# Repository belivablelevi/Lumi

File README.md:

# Lumi

**An open-source, build-it-yourself robot keychain pet.** A tiny glowing face
that feels your pats and shakes, has moods, sleeps when you put it down,
wakes when you pick it up, and plays ping-pong with a friend's
Lumi over the air.

Lumi is an independent DIY recreation of the *kind* of gadget popularised by
the Rekko NEO keychain. It's built from ~$15 of off-the-shelf modules. It
shares no code, artwork or branding with Rekko and isn't affiliated with it.

| Spec card item | Lumi |
|---|---|
| 0.96" OLED, 128×64, glowing cyan | SSD1306 0.96" 128×64 (blue panel reads as cyan) |
| Motion sensor, 6-axis, feels every pat & shake | MPU-6050: pat, double-pat, pat-spam, shake, drop, tilt, flip, pick-up, put-down |
| ESP32-C3 brain, runs 60+ animations | XIAO ESP32C3 · **64 animations** from 29 parametric expressions, plus blinking, eye-darts and breathing on top |
| 2-player wireless battle | **Tilt Pong** over ESP-NOW: classic Pong across two screens. Tilt to move your paddle, pat to smash, first to 5 |
| Battery inside | 702025 300 mAh LiPo (the case can be resized for others) |
| USB-C rechargeable | XIAO's USB-C + on-board charger |
| Deep-sleeps when idle | ESP32-C3 deep sleep, display off, IMU on wake-on-motion |
| Wakes when you pick it up | MPU-6050 motion interrupt → GPIO3 deep-sleep wake |
| Free animation updates | Wi-Fi update mode: phone → `192.168.4.1` → upload |
| 35 × 37 mm glitter shell | Parametric OpenSCAD snap-fit case, 35 × 37 × 25.5 mm, print in glitter PLA |

## What it looks like

All 29 expressions (rendered by the real firmware code in the simulator):

Menu, battery, update and Tilt Pong screens:

A scripted session: boot, pats, shake, menu, a full Tilt Pong match, falling asleep
([tour.gif](docs/previews/tour.gif)).

## Every Lumi is one of a kind

Each unit has its own eyes, highlight, accent and temperament: 108,000
combinations, with common, uncommon, rare and legendary units. A unit gets
its personality automatically from its chip ID. Makers can also assign
one at the factory with **Lumi Studio**, a desktop app (Windows, macOS,
Linux) for:

- designing new faces and animations,
- generating batches of unique units with a rarity mix you choose,
- writing each unit's persona over USB and recording it in a manifest.

See [docs/studio.md](docs/studio.md).

## The website

`web/` is the Snaggo storefront for Lumi, at [snaggo.tech](https://snaggo.tech). It's a Next.js site with pre-orders through Stripe, launch emails, and the
firmware's real animations playing on every screen. See [web/README.md](web/README.md).

## Repository layout

```
firmware/
  platformio.ini            PlatformIO project (XIAO ESP32C3)
  src/                      hardware glue: main.cpp, OLED + IMU drivers, config.h (pins & tuning)
  lib/lumi_core/src/        portable brain, no Arduino dependencies:
    face.*                    parametric face renderer + 29 expressions
    animations.*              64 animations (data tables; add your own here or in Lumi Studio)
    genes.*                   per-unit looks, temperament and rarity
    pack.*                    emotion packs: custom faces, animations and a persona
    serial_cmd.*              USB provisioning protocol
    animator.*                tweening, blinking, eye darts, motion layers
    gestures.*                pat / shake / tilt / pickup / freefall detection
    mood.h                    happiness + energy, persisted across deep sleep
    pong.*                    Tilt Pong: pairing, ball hand-off over the radio, scoring
    app.*                     behaviour: modes, menu, sleep rules, screens
    gfx.*                     1-bit framebuffer + 5x7 font
hardware/
  BOM.md · wiring.md
  enclosure/lumi_case.scad  parametric case; stl/ has ready-to-print parts
docs/
  using-lumi.md             gestures, mood, menu, Tilt Pong, OTA, serial console
  assembly.md               build guide + first-power-up checklist
  studio.md                 Lumi Studio guide for makers
  previews/                 rendered images
tests/                      desktop tests for the core (make -C tests)
tools/
  sim/                      desktop simulator → PNG/GIF previews
  studio/                   Lumi Studio desktop app (PySide6) + liblumicore C API + virtual Lumi
web/                        the Snaggo website (Next.js storefront, pre-orders, launch signups)
  arduino_build.sh          build with arduino-cli / Arduino IDE instead of PlatformIO
```

## Build the firmware

**PlatformIO** (recommended):

```sh
cd firmware
pio run -t upload        # build + flash over USB-C
pio device monitor       # serial console (type 'h' for commands)
```

**arduino-cli / Arduino IDE** (ESP32 core 2.0.17):

```sh
tools/arduino_build.sh                # compile
tools/arduino_build.sh /dev/ttyACM0   # compile + upload
```

Using an **ESP32-S3 SuperMini** instead of the XIAO? Build with
`pio run -e esp32s3_supermini -t upload`, and see the S3 section of
[`hardware/wiring.md`](hardware/wiring.md#alternative-esp32-s3-supermini) for its
pins, power options and the matching case setting.

If the XIAO doesn't show up as a serial port, hold **BOOT**, tap **RESET**,
release **BOOT**, then upload again.

## Hack on it without hardware

The behaviour runs on your computer exactly as it does on the device:

```sh
make -C tests                         # 819 checks: gestures, pong, animations, genes, packs, app flows
python3 tools/sim/make_previews.py    # re-render docs/previews (needs Pillow)
python3 tools/sim/make_previews.py --all-gifs   # one GIF per animation in build/sim/gifs
```

Adding an animation is a few lines in `firmware/lib/lumi_core/src/animations.cpp`:
a list of `(expression, gaze, motion, tween ms, hold ms, effects)` keys
plus a table row saying which gesture triggers it and in which mood range.

## How it works (short version)

- **Face**: a face is ~20 numbers (eye size, lids, slant, cheeks, gaze, mouth
  shape…). Expressions are presets, and animations tween between them.
  Blinks, eye darts and breathing are layered on top, so Lumi never looks
  frozen.
- **Gestures**: the MPU-6050 samples at 100 Hz into its FIFO. The firmware
  high-passes the signal. Short sharp bursts are pats, repeated big bursts
  are shakes. Low-passed gravity gives orientation; |a| ≈ 0 is free-fall.
  Tap timestamps come from the FIFO cadence, so they stay accurate even
  while the display is being redrawn.
- **Tilt Pong**: ESP-NOW broadcast, no pairing. The Lumi with the higher
  MAC hosts and serves first. Tilt steers the paddle (low-passed gravity
  X). Only the Lumi the ball is on decides whether it was hit, so radio latency just makes the flight a little longer. Each
  ball crossing the net carries a sequence number plus its position, angle
  and speed, and each Lumi's miss count only ever grows. Packets repeat
  ~10 times a second, so lost ones only add delay. The tests play whole
  matches, and 90-second rallies, over a simulated link with 40% packet loss.
- **Sleep**: display charge pump off, IMU to low-power cycle mode with a
  latched motion interrupt on GPIO3, ESP32-C3 into deep sleep. Mood lives
  in RTC memory, and the RTC clock tells Lumi how long it slept.

## Status

- ✅ Core logic: 819 automated checks pass (ASan/UBSan clean), including
  two simulated Lumis playing complete Tilt Pong matches through their menus.
- ✅ Lumi Studio: 13 tests drive every tab offscreen and provision a virtual
  Lumi end to end. The packaged Linux app was built and started here. CI
  builds Windows and macOS too, but they haven't been tried by a person yet.
- ✅ Firmware compiles and links for the ESP32-C3 and ESP32-S3 (Arduino core
  2.0.17, `-Wall -Wextra`, no warnings in Lumi's code). On the C3 it uses
  812 KB of flash (63% of an OTA slot) and 87 KB of RAM.
- ✅ Case renders to valid STLs at 35 × 37 mm.
- ⚠️ **Not yet tested on real hardware.** Expect to tune the IMU axis map,
  tap threshold and wake sensitivity once it's built (see the checklist in
  `docs/assembly.md`), and to adjust case tolerances after a test print.
- ⚠️ The case is 25.5 mm deep because a stock GY-521 board won't fit beside
  the XIAO. A custom PCB, or a smaller IMU breakout, could get it thinner.

## License

MIT, see [LICENSE](LICENSE).

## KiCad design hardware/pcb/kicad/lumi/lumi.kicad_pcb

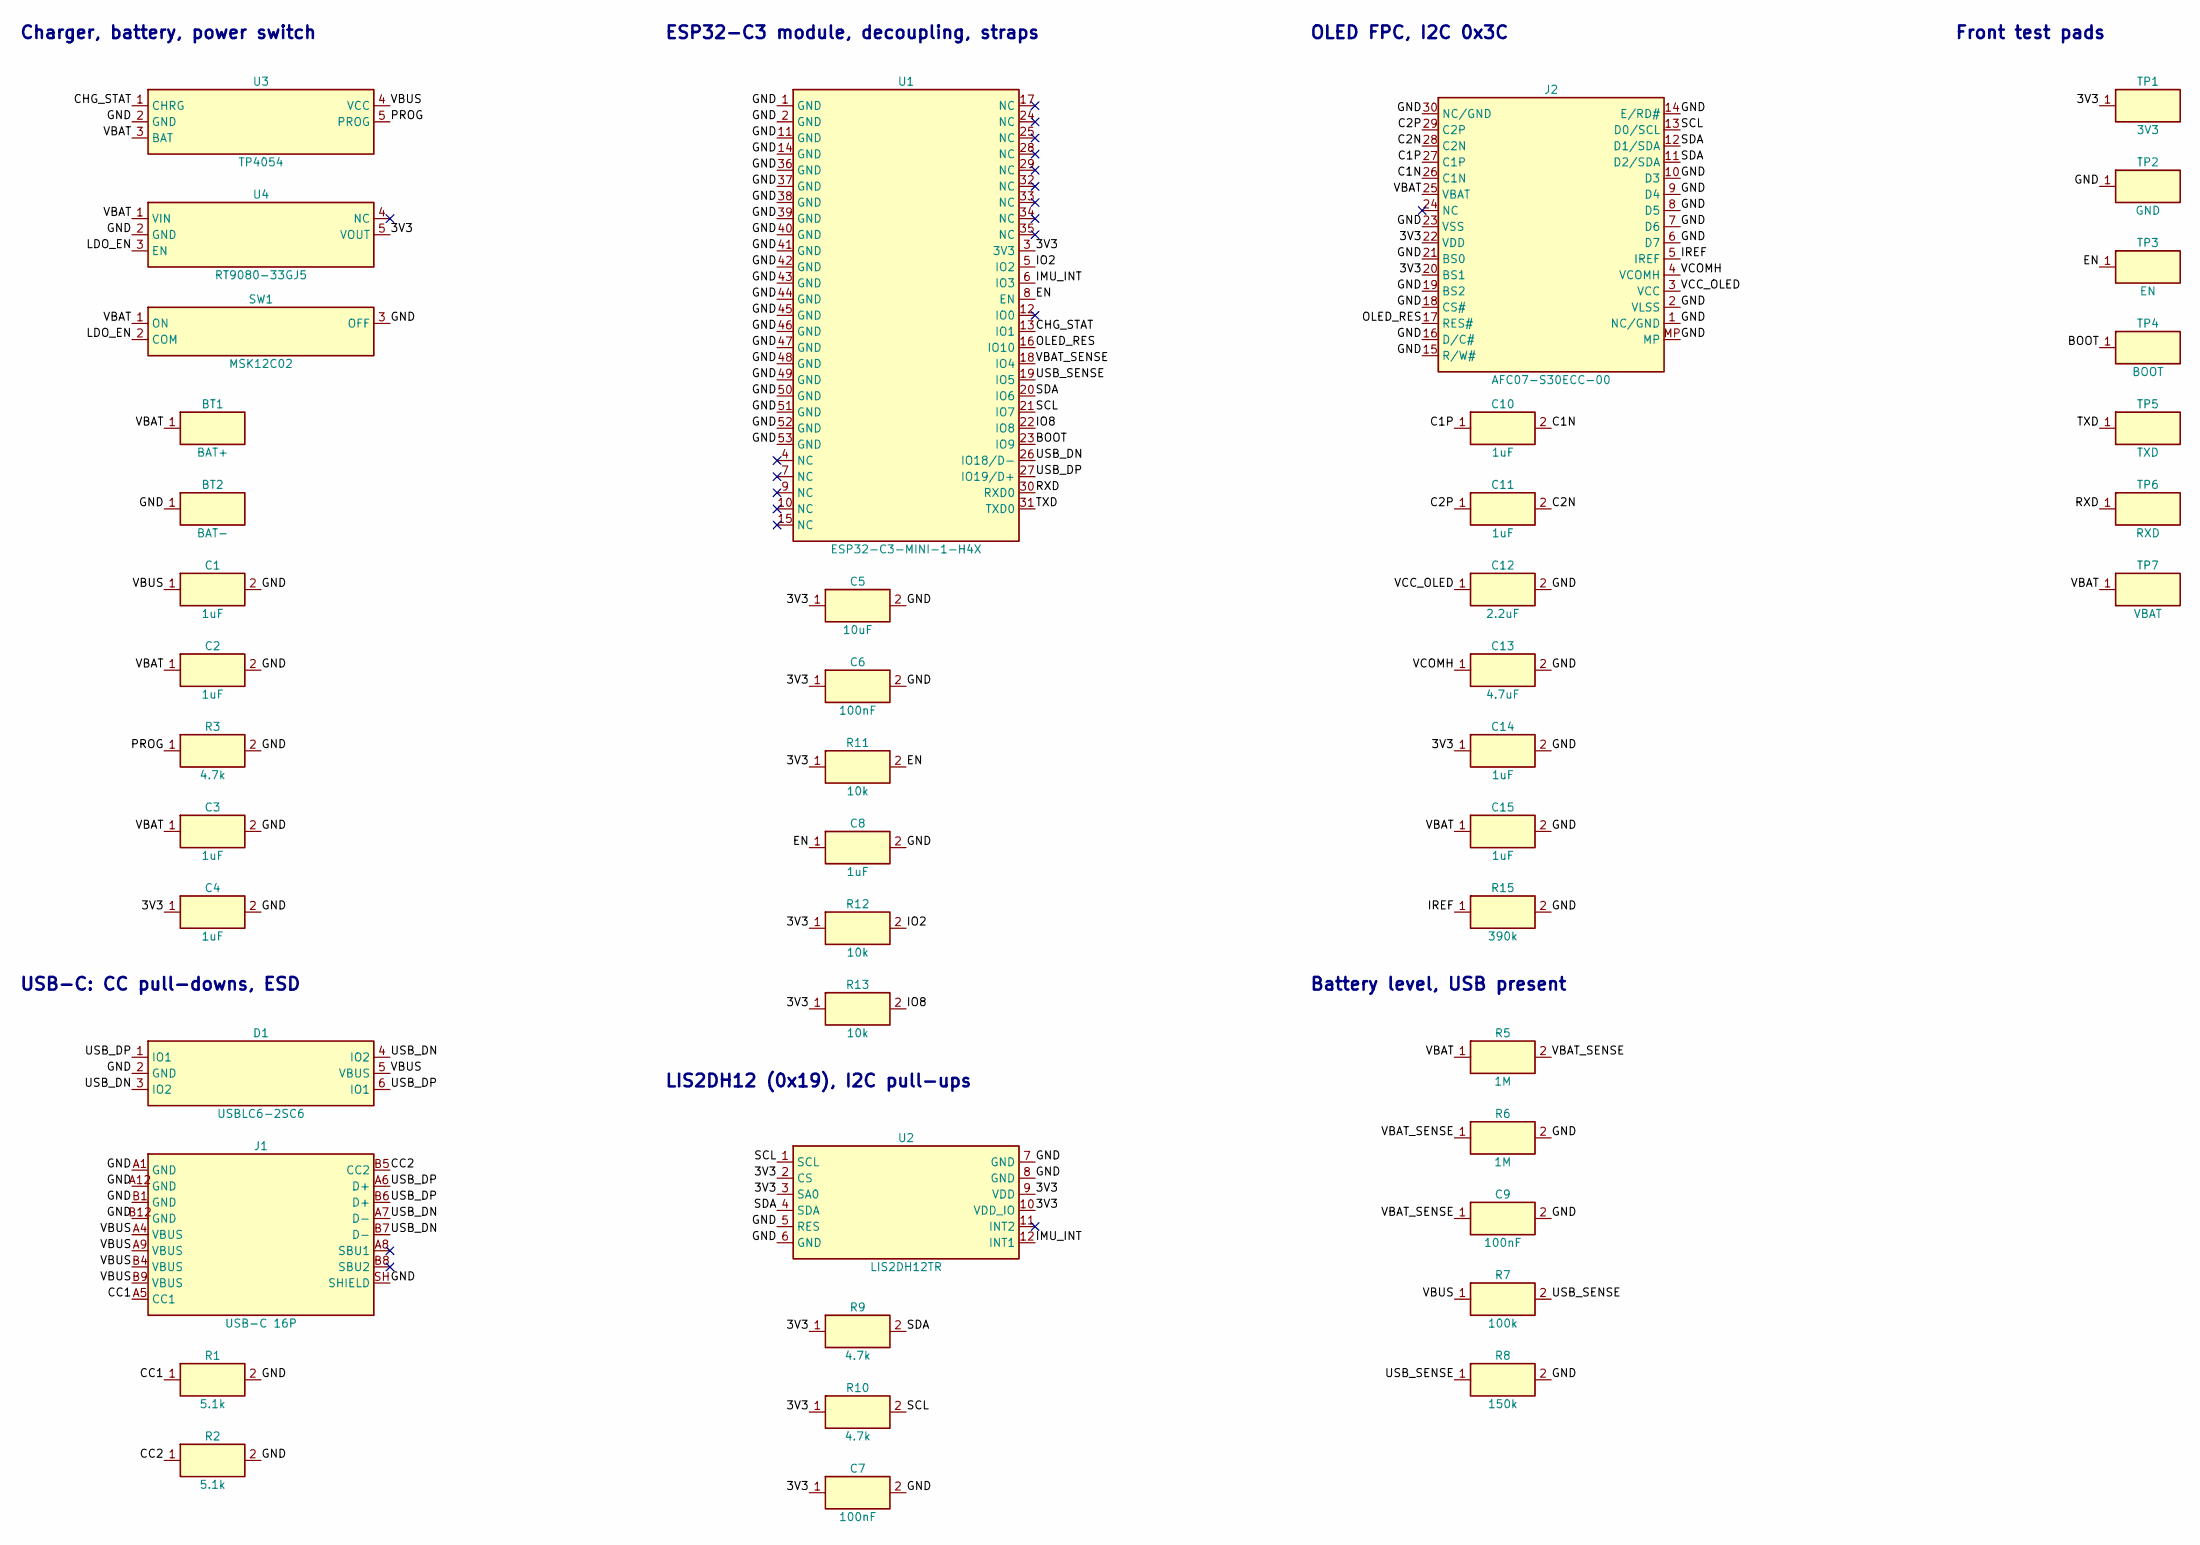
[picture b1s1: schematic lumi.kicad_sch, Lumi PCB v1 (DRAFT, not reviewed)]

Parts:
BT1: BAT+; TestPoint_Pad_1.5x1.5mm
BT2: BAT-; TestPoint_Pad_1.5x1.5mm
C1, C2, C3, C4, C8, C10, C11, C14, C15: 1uF; C_0402_1005Metric; LCSC C52923
C5: 10uF; C_0402_1005Metric; LCSC C15525
C6, C7, C9: 100nF; C_0402_1005Metric; LCSC C1525
C12: 2.2uF; C_0603_1608Metric; LCSC C23630
C13: 4.7uF; C_0603_1608Metric; LCSC C19666
D1: USBLC6-2SC6; SOT-23-6; LCSC C7519
J1: USB-C 16P; USB_C_Receptacle_HRO_TYPE-C-31-M-12; LCSC C165948
J2: AFC07-S30ECC-00; JUSHUO_AFC07-S30ECC-00; LCSC C11095
R1, R2: 5.1k; R_0402_1005Metric; LCSC C25905
R3, R9, R10: 4.7k; R_0402_1005Metric; LCSC C25900
R5, R6: 1M; R_0402_1005Metric; LCSC C26083
R7: 100k; R_0402_1005Metric; LCSC C25741
R8: 150k; R_0402_1005Metric; LCSC C25755
R11, R12, R13: 10k; R_0402_1005Metric; LCSC C25744
R15: 390k; R_0402_1005Metric; LCSC C25782
SW1: MSK12C02; LCSC C431540
TP1: 3V3; TestPoint_Pad_D1.0mm
TP2: GND; TestPoint_Pad_D1.0mm
TP3: EN; TestPoint_Pad_D1.0mm
TP4: BOOT; TestPoint_Pad_D1.0mm
TP5: TXD; TestPoint_Pad_D1.0mm
TP6: RXD; TestPoint_Pad_D1.0mm
TP7: VBAT; TestPoint_Pad_D1.0mm
U1: ESP32-C3-MINI-1-H4X; ESP32-C3-MINI-1; LCSC C41349510
U2: LIS2DH12TR; LGA-12_2x2mm_P0.5mm; LCSC C110926
U3: TP4054; SOT-23-5; LCSC C32574
U4: RT9080-33GJ5; SOT-23-5; LCSC C841192

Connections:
3V3: C4.1, C5.1, C6.1, C7.1, C14.1, J2.20 (BS1), J2.22 (VDD), R9.1, R10.1, R11.1, R12.1, R13.1, TP1.1, U1.3 (3V3), U2.2 (CS), U2.3 (SA0), U2.9 (VDD), U2.10 (VDD_IO), U4.5 (VOUT)
BOOT: TP4.1, U1.23 (IO9)
C1N: C10.2, J2.26 (C1N)
C1P: C10.1, J2.27 (C1P)
C2N: C11.2, J2.28 (C2N)
C2P: C11.1, J2.29 (C2P)
CC1: J1.A5 (CC1), R1.1
CC2: J1.B5 (CC2), R2.1
CHG_STAT: U1.13 (IO1), U3.1 (CHRG)
EN: C8.1, R11.2, TP3.1, U1.8 (EN)
GND: BT2.1, C1.2, C2.2, C3.2, C4.2, C5.2, C6.2, C7.2, C8.2, C9.2, C12.2, C13.2, C14.2, C15.2, D1.2 (GND), J1.A1 (GND), J1.A12 (GND), J1.B1 (GND), J1.B12 (GND), J1.SH (SHIELD), J2.1 (NC/GND), J2.2 (VLSS), J2.6 (D7), J2.7 (D6), J2.8 (D5), J2.9 (D4), J2.10 (D3), J2.14 (E/RD#), J2.15 (R/W#), J2.16 (D/C#), J2.18 (CS#), J2.19 (BS2), J2.21 (BS0), J2.23 (VSS), J2.30 (NC/GND), J2.MP, R1.2, R2.2, R3.2, R6.2, R8.2, R15.2, SW1.3 (OFF), TP2.1, U1.1 (GND), U1.2 (GND), U1.11 (GND), U1.14 (GND), U1.36 (GND), U1.37 (GND), U1.38 (GND), U1.39 (GND), U1.40 (GND), U1.41 (GND), U1.42 (GND), U1.43 (GND), U1.44 (GND), U1.45 (GND), U1.46 (GND), U1.47 (GND), U1.48 (GND), U1.49 (GND), U1.50 (GND), U1.51 (GND), U1.52 (GND), U1.53 (GND), U2.5 (RES), U2.6 (GND), U2.7 (GND), U2.8 (GND), U3.2 (GND), U4.2 (GND)
IMU_INT: U1.6 (IO3), U2.12 (INT1)
IO2: R12.2, U1.5 (IO2)
IO8: R13.2, U1.22 (IO8)
IREF: J2.5 (IREF), R15.1
LDO_EN: SW1.2 (COM), U4.3 (EN)
OLED_RES: J2.17 (RES#), U1.16 (IO10)
PROG: R3.1, U3.5 (PROG)
RXD: TP6.1, U1.30 (RXD0)
SCL: J2.13 (D0/SCL), R10.2, U1.21 (IO7), U2.1 (SCL)
SDA: J2.11 (D2/SDA), J2.12 (D1/SDA), R9.2, U1.20 (IO6), U2.4 (SDA)
TXD: TP5.1, U1.31 (TXD0)
USB_DN: D1.3 (IO2), D1.4 (IO2), J1.A7 (D-), J1.B7 (D-), U1.26 (IO18/D-)
USB_DP: D1.1 (IO1), D1.6 (IO1), J1.A6 (D+), J1.B6 (D+), U1.27 (IO19/D+)
USB_SENSE: R7.2, R8.1, U1.19 (IO5)
VBAT: BT1.1, C2.1, C3.1, C15.1, J2.25 (VBAT), R5.1, SW1.1 (ON), TP7.1, U3.3 (BAT), U4.1 (VIN)
VBAT_SENSE: C9.1, R5.2, R6.1, U1.18 (IO4)
VBUS: C1.1, D1.5 (VBUS), J1.A4 (VBUS), J1.A9 (VBUS), J1.B4 (VBUS), J1.B9 (VBUS), R7.1, U3.4 (VCC)
VCC_OLED: C12.1, J2.3 (VCC)
VCOMH: C13.1, J2.4 (VCOMH)

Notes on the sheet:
Charger, battery, power switch
USB-C: CC pull-downs, ESD
ESP32-C3 module, decoupling, straps
LIS2DH12 (0x19), I2C pull-ups
OLED FPC, I2C 0x3C
Battery level, USB present
Front test pads

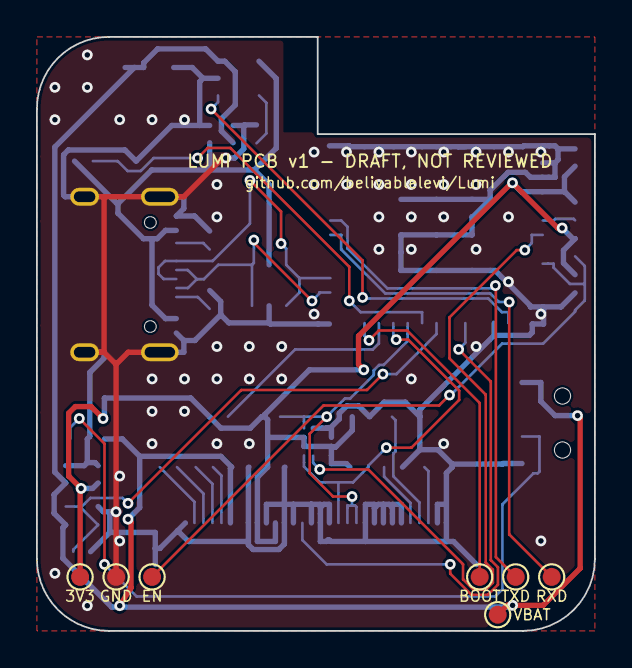
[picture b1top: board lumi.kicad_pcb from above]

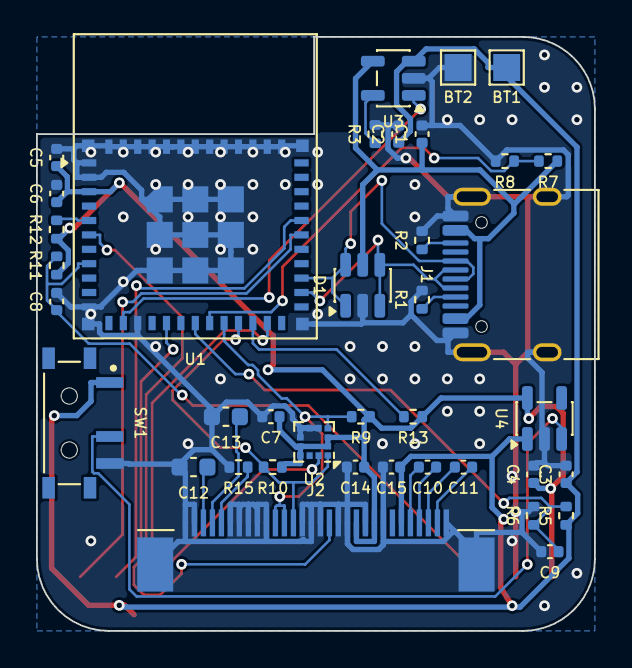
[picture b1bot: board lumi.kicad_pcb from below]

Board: 2 copper layers, 31.0 x 33.0 mm, 45 parts (38 on the bottom side), 30 nets.

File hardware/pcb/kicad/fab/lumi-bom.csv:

Comment,Designator,Footprint,LCSC Part #
1uF,"C1,C2,C3,C4,C8,C10,C11,C14,C15",C_0402_1005Metric,C52923
2.2uF,C12,C_0603_1608Metric,C23630
4.7uF,C13,C_0603_1608Metric,C19666
10uF,C5,C_0402_1005Metric,C15525
100nF,"C6,C7,C9",C_0402_1005Metric,C1525
USBLC6-2SC6,D1,SOT-23-6,C7519
USB-C 16P,J1,USB_C_Receptacle_HRO_TYPE-C-31-M-12,C165948
AFC07-S30ECC-00,J2,JUSHUO_AFC07-S30ECC-00,C11095
5.1k,"R1,R2",R_0402_1005Metric,C25905
10k,"R11,R12,R13",R_0402_1005Metric,C25744
390k,R15,R_0402_1005Metric,C25782
4.7k,"R3,R9,R10",R_0402_1005Metric,C25900
1M,"R5,R6",R_0402_1005Metric,C26083
100k,R7,R_0402_1005Metric,C25741
150k,R8,R_0402_1005Metric,C25755
MSK12C02,SW1,MSK12C02,C431540
ESP32-C3-MINI-1-H4X,U1,ESP32-C3-MINI-1,C41349510
LIS2DH12TR,U2,LGA-12_2x2mm_P0.5mm,C110926
TP4054,U3,SOT-23-5,C32574
RT9080-33GJ5,U4,SOT-23-5,C841192
